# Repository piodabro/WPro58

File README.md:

# WPro58 for Eachine PRO58 and Quanum HB5808 modules.
STM32 MCU based diversity module firmware.

This firmware uses some code from [Shea Ivey's rx5808-pro](https://github.com/sheaivey/rx5808-pro-diversity) 

If you like this work and you're buying Eachine PRO58 please use this link:
[Eachine PRO58](https://www.banggood.com/Eachine-PRO58-RX-Diversity-40CH-5_8G-OLED-SCAN-VRX-FPV-Receiver-for-FatShark-Goggles-p-1160357.html?p=CL07182964413201511Q)
(It's a reflink)

### Pinouts and flashing.

To flash your PRO58 or HB5808 module you have to use ST-link programmer.
The best way to flash your module is:
1. Connect 5V power and GND via Fatshark connector - Use 5V BEC with at least 1A of current,
2. Connect GND, SWDIO and SWDCLK to ST-Link via SWD connector (on top left corner of module - see images).
3. Use ST-LINK Utility from ST web page - http://www.st.com/en/development-tools/stsw-link004.html - look on the bottom of page for download.
4. If its brand new module you have to remove _Read Out Protection_. In ST-LINK Utility Click on _Target -> Option Bytes..._ .
Set _Read Out Protection_ to _Disabled_ and next click _Apply_ (**_WARNING_**: This will erase original firmware - there is no way back). Do not touch other things in this menu.
5. Load .bin file by clicking Open file button, and next _Target -> Program and verify..._
6. Once it finish witout error you have WPro58 installed. Disconnect all and then reconnect power ;)

Remember that module draws ~0.4A of current, power it with efficient power supply!

To edit/build code you need to download [SW4STM32](http://www.openstm32.org/HomePage) IDE (Eclipse based)

#### Eachine PRO58 pinouts

___

#### Quanum HB5808 pinouts

FatShark pins are not connected to MCU.
___

### Big thanks to
- **Telekatz** for OSD overlay implementation !!!
- **mihero** for contributing
- **20Sy** for HB5808 module ;)
- **conkerkh** for contributing

#### Warning!
If you use module with FatShark goggles make sure that FS pins mode setting is set to FS (not BUTTON).
This settings changes pullup settings on FS channel pins.

To use BUTTON mode simply add buttons that connect pin to ground when pressed.

___

<br />This work is licensed under a <a rel="license" href="http://creativecommons.org/licenses/by-nc-sa/4.0/">Creative Commons Attribution-NonCommercial-ShareAlike 4.0 International License</a>.

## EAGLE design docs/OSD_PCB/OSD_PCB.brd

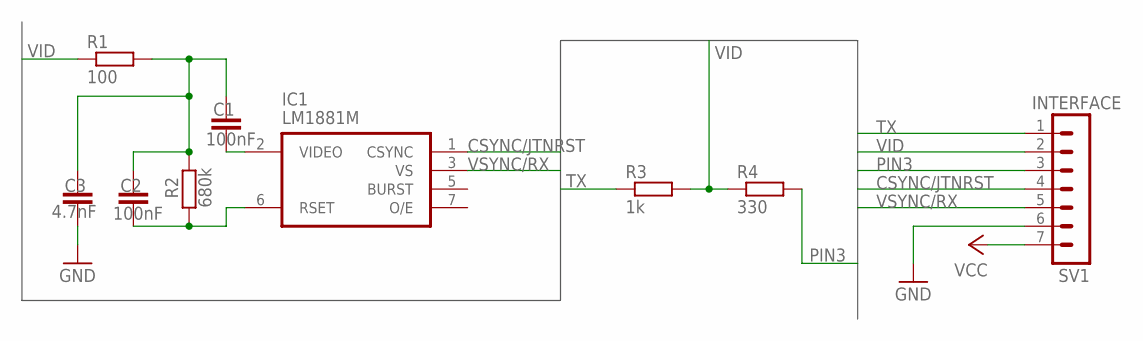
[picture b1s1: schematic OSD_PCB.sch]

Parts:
C1, C2: 100nF; C0603
C3: 4.7nF; C0603
IC1: LM1881M; SO08
R1: 100; R0603
R2: 680k; R0603
R3: 1k; R0603
R4: 330; R0603
SV1: INTERFACE; MA07-1

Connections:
CSYNC/JTNRST: IC1.1 (CSYNC), SV1.4
GND: C3.2, IC1.4 (GND), SV1.6
unnamed: C1.2, IC1.2 (VIDEO)
unnamed: C2.2, IC1.6 (RSET), R2.1
unnamed: C1.1, C2.1, C3.1, R1.2, R2.2
PIN3: R4.2, SV1.3
TX: R3.1, SV1.1
VCC: IC1.8 (VCC), SV1.7
VID: R1.1, R3.2, R4.1, SV1.2
VSYNC/RX: IC1.3 (VS), SV1.5

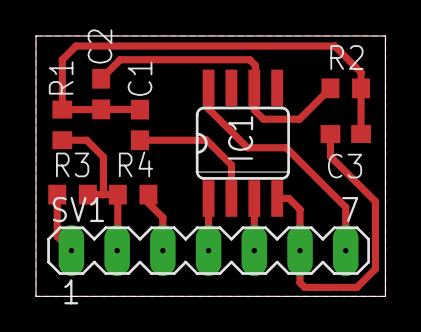
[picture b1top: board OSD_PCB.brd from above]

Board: 2 copper layers, 19.4 x 14.5 mm, 9 parts (0 on the bottom side), 10 nets.

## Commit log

2017-08-20 relese
2017-08-22 pro58 pinouts
2017-08-22 rename
2017-08-22 imgs
2017-09-13 v0.2 release
2017-10-10 release v0.3
2017-10-11 v0.3 built on other optimization levels
2017-10-12 v0.3 fixed FS buttons issue
2017-11-06 public open code
2017-11-06 v0.4 release
2017-11-09 Fix project paths
    Fix absolute paths on project
2017-11-09 Add fatshark button handler to screensaver
    Handle fatshark button when in screensaver state
2017-11-09 Reset timer on fs buttons
    Nicer screensaver resetting timer if channel change with fs buttons
2017-11-19 Callsign on screensaver
    Read callsign from settings and draw on screensaver
    callsign is set from #define CALLSIGN
2017-11-29 callsign modifiable
    Callsign is now modifiable
    Reads from eeprom settings
    saves only if it has changed
2017-11-30 Fixed callsign icon
    person icon for callsign screen
2017-12-03 Callsign 10 char len and draw fixes
    Fix drawing of callsign
    extend to 10 char callsign
    allow exit from settings without save
2017-12-04 Fix up/down crash
    ignore up/down if cursor is -1
2017-12-05 project structure rebuild, new CubeMX configuration, TIM3 at 400Hz interrupt
2017-12-17 Unittest enabling
    initial setup of unittest
2017-12-17 gtest is user env dep
    new makefile to define user specific stuff
2017-12-19 Fixing unittest and adding initial filters
    Adding initial filters to verify unittesting
    fixing UT make
2017-12-21 Change float to integer calculation
    change filters to not use float
2017-12-29 v0.5 release
2018-01-05 favourites untested
2018-01-09 EEprom magic
2018-02-06 HB5808 version first commit
2018-02-07 partial flash emulated eeprom
2018-02-07 HB5808 flash eeprom emulation, A/B channels switching fixes, UI fixes
2018-02-07 Buzzer and FSpins on USE_* defines instead HB5808 define
2018-02-07 HB5808 pinouts
2018-02-07 doc update
2018-02-07 HB5808 schematic
2018-02-08 selecting EEPROM type using USE_EXTERNAL_EEPROM define, change Favorites position in menu
2018-02-08 fix EXT_EEPROM define in header, fix default favourite channels memcpy
2018-02-08 v0.6 release, first HB5808 version
2018-02-08 release .bin rename
2018-02-09 Emulated eeprom library comment
2018-02-09 new settings menu, buzzer option
2018-02-10 long press mode to exit to settings menu from fav options
2018-02-10 screensaver disable setting
2018-02-10 rssi calibration, visible values during scan
2018-02-10 fix channel in search after bandscan/calibration
2018-02-10 Single antenna diversity mode searching fix, display only selected antenna graphs
2018-02-11 Move graph UI to a base class for fav/search screens, cleanup some commented out code, move beeper welcome sound to Beeper class function, move initial logo display to Ui class function, cleanup rece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
2018-02-14 Display lib description update
2018-02-18 Add 500ms watchdog, delay func with Watchdog reset, regenerated cube base code, move cube project to separate dir
2018-02-19 add .gitignore new line at the end
2018-02-22 v0.7 release
2018-03-03 menu scrolling
2018-03-03 settings menu arrows
2018-03-04 Screen flip
2018-03-04 FS pins as buttons option
2018-03-04 v0.8 pre-alpha1 release
2018-03-11 HAL+CMSIS update.
2018-03-11 DMA screen updates, parallel building, add IT for I2C1
2018-03-11 Fix I2C Reset.
2018-03-12 HB5808 fixes
2018-03-24 Clean channel storing and selection
    refactor code to be more clean
2018-03-24 Save fs button selected channel
    save to settings last channel selected with fs buttons
2018-05-18 update branch
2018-05-31 fix HB5808 display DMA handling
2018-06-05 FatShark pins initial button mode build configuration
2018-06-08 v0.9 release commit
2018-07-21 add OSD, add OSD58 device
2018-07-22 Add OSD settings menu
2018-07-22 make LCD optional with OSD
2018-07-28 Add OSD to PRO58
2018-07-29 Fix OSD58
2018-07-29 Fix OSD sync switching Add OSD58 schematic
2018-07-30 Use of TIM1 for OSD
2018-08-01 Change sync mode in menues
2018-08-04 OSD overlay for PRO58
2018-10-03 OSD overlay mod PCB
2018-10-05 New OSD RSSI bar
2018-10-05 cleaned up configurations for PRO58 OSD
2018-10-15 OSD overlay PCB documentation, refactor main.h hardware configurations - put HW defines to separate files.
2018-10-15 HB5808 and FS_PINS refactor
2018-10-16 PCB bugfix, move bar a little lower
2018-10-18 update OSD PCB
2018-10-24 new PCB version + eagle PCB version
